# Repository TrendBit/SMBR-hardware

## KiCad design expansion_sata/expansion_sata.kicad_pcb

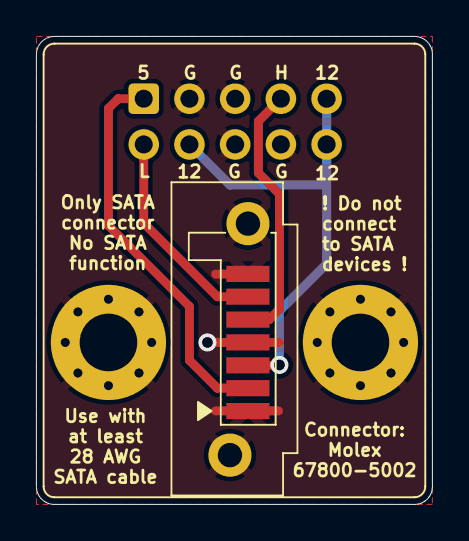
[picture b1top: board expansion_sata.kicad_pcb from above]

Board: 2 copper layers, 22.0 x 26.0 mm, 4 parts (1 on the bottom side), 5 nets.

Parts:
H1, H2: M3; MountingHole_3.2mm_M3_Pad_Via
J1: Conn_01x07_MountingPin; Molex_SATA_67800-5002_Vertical_SMD
J2: 2.54-2*5P; IDC-Header_2x05_P2.54mm_Vertical

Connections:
+5V: J1.2, J2.1
+12V: J1.3, J2.4, J2.9, J2.10
/CAN_H: J1.5, J2.7
/CAN_L: J1.6, J2.2
GND: H1.1, H2.1, J1.1, J1.4, J1.7, J1.MP (MountPin), J2.3, J2.5, J2.6, J2.8

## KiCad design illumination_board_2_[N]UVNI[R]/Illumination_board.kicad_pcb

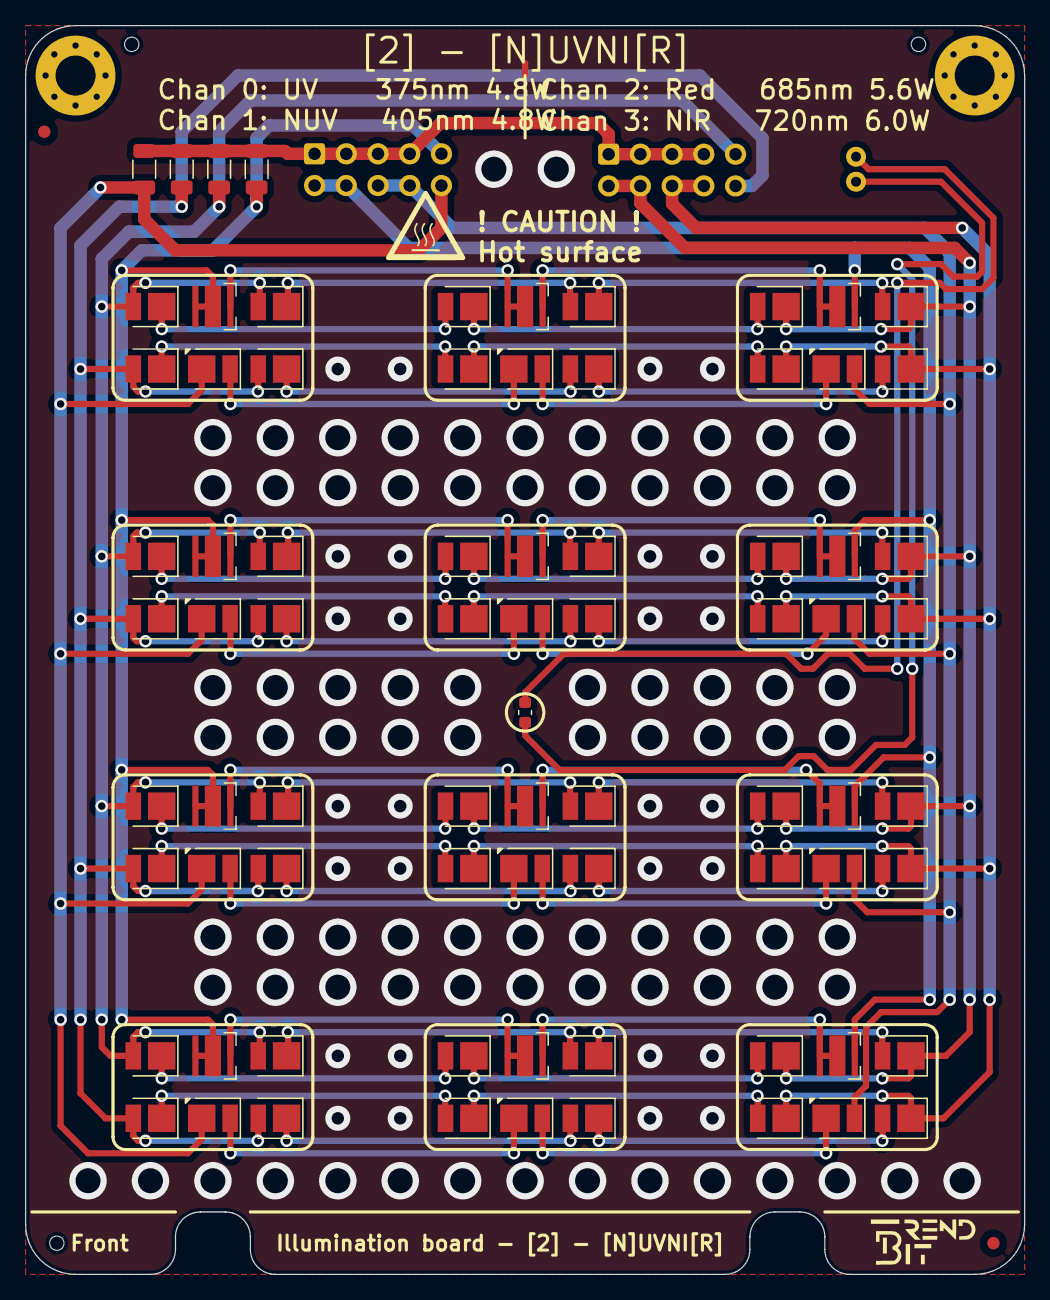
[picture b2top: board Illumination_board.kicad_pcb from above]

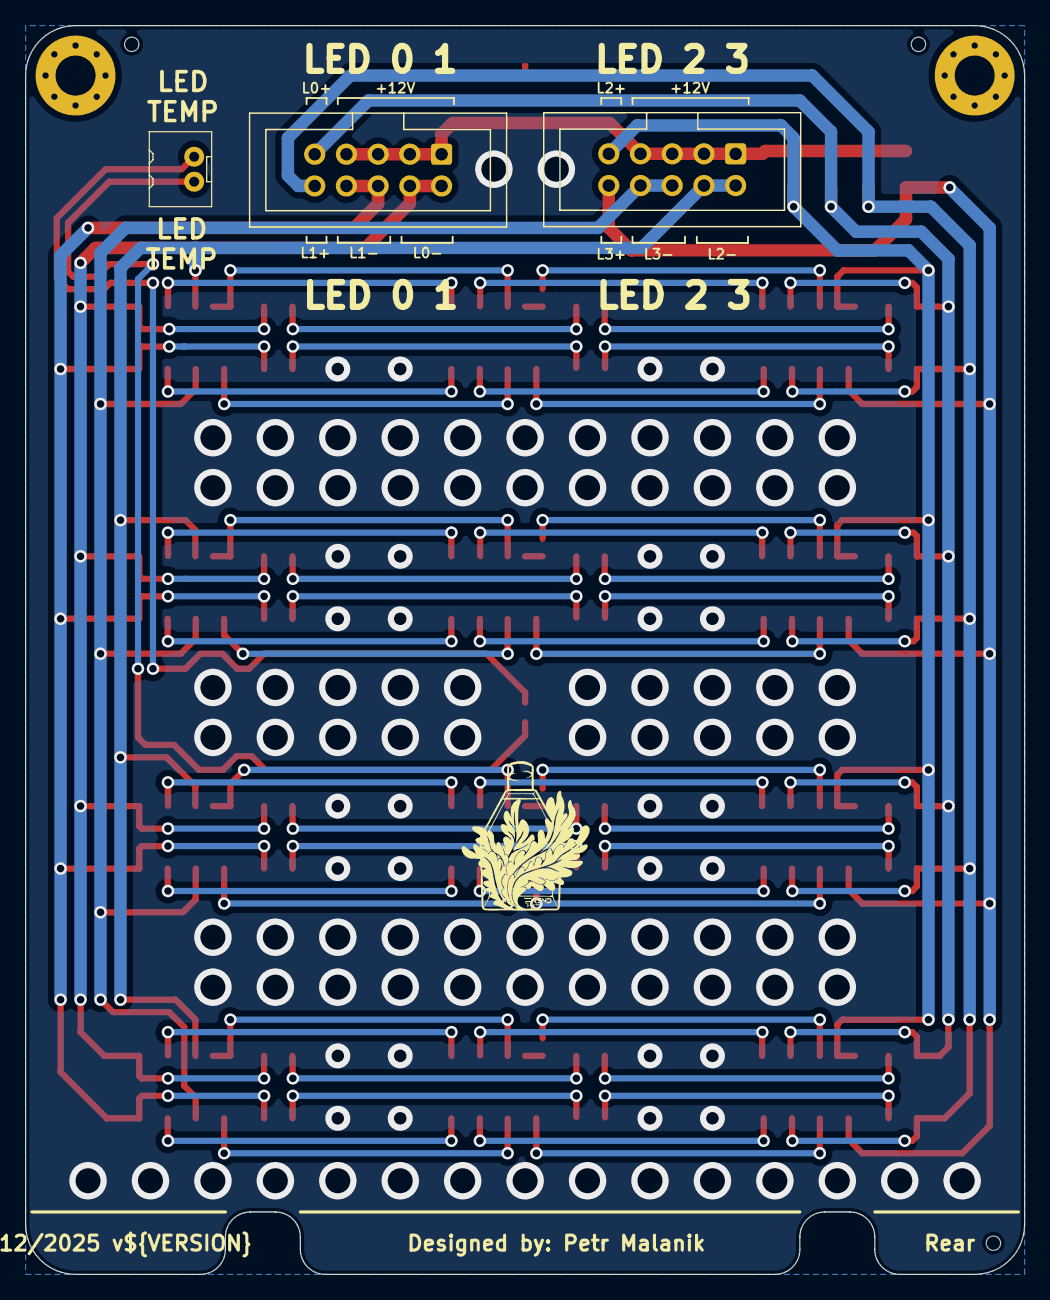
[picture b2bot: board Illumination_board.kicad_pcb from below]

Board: 2 copper layers, 80.0 x 100.0 mm, 88 parts (3 on the bottom side), 60 nets.

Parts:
D1, D2, D3, D4, D5, D6, D7, D8, D9, D10, D11, D12, D13, D14, D15, D16, D17, D18, D19, D20, D21, D22, D23, D24: XL-2835UVA-02; LED_PLCC_2835
D25, D26, D27, D28, D29, D30, D31, D32, D33, D34, D35, D36, D37, D38, D39, D40, D41, D42, D43, D44, D45, D46, D47, D48: P2835P1UVS3G12; LED_PLCC_2835
D49, D50, D51, D52, D53, D54, D55, D56, D57, D58, D59, D60: LEHR0113W120; LED_LEHR01113E-XHP35_3.5mmx3.5mm
D61, D62, D63, D64, D65, D66, D67, D68, D69, D70, D71, D72: JE2835AFR; LED_PLCC_2835_Reversed
FID1, FID2, FID3: TLH; ToolingHole_JLCPCB
FID4, FID5: 0.5/1mm; Fiducial_1mm_Mask2mm
H1, H2: M3; MountingHole_3.2mm_M3_Pad_Via
J1: DF3A-2P-2DSA; Hirose_DF3A-02P-2DSA_1x02_P2.00mm_Vertical
J2, J3: 2.54-2*5P; IDC-Header_2x05_P2.54mm_Vertical
NT1: Slug; NetTie-2_SMD_Pad0.5mm
R1, R2: 220mR; R_1206_3216Metric
R3, R4: 120mR; R_1206_3216Metric
TH1: 10k, 3950b; L_0603_1608Metric

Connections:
+12V: J2.1, J2.3, J2.5, J2.7, J3.1, J3.3, J3.5, J3.7, R1.1, R2.1, R3.1, R4.1
/LED_0+: D1.2 (A), D4.2 (A), D7.2 (A), D10.2 (A), D13.2 (A), D16.2 (A), D19.2 (A), D22.2 (A), J2.9, R1.2
/LED_0-: D3.1 (K), D6.1 (K), D9.1 (K), D12.1 (K), D15.1 (K), D18.1 (K), D21.1 (K), D24.1 (K), J2.2, J2.4
/LED_1+: D25.2 (A), D28.2 (A), D31.2 (A), D34.2 (A), D37.2 (A), D40.2 (A), D43.2 (A), D46.2 (A), J2.10, R2.2
/LED_1-: D27.1 (K), D30.1 (K), D33.1 (K), D36.1 (K), D39.1 (K), D42.1 (K), D45.1 (K), D48.1 (K), J2.6, J2.8
/LED_2+: D49.2 (A), D52.2 (A), D55.2 (A), D58.2 (A), J3.9, R3.2
/LED_2-: D51.1 (K), D54.1 (K), D57.1 (K), D60.1 (K), J3.2, J3.4
/LED_3+: D61.2 (A), D64.2 (A), D67.2 (A), D70.2 (A), J3.10, R4.2
/LED_3-: D63.1 (K), D66.1 (K), D69.1 (K), D72.1 (K), J3.6, J3.8
/SLUG: NT1.1, NT1.2
unnamed: D1.1 (K), D2.2 (A)
unnamed: D2.1 (K), D3.2 (A)
unnamed: D4.1 (K), D5.2 (A)
unnamed: D5.1 (K), D6.2 (A)
unnamed: D7.1 (K), D8.2 (A)
unnamed: D8.1 (K), D9.2 (A)
unnamed: D10.1 (K), D11.2 (A)
unnamed: D11.1 (K), D12.2 (A)
unnamed: D13.1 (K), D14.2 (A)
unnamed: D14.1 (K), D15.2 (A)
unnamed: D16.1 (K), D17.2 (A)
unnamed: D17.1 (K), D18.2 (A)
unnamed: D19.1 (K), D20.2 (A)
unnamed: D20.1 (K), D21.2 (A)
unnamed: D22.1 (K), D23.2 (A)
unnamed: D23.1 (K), D24.2 (A)
unnamed: D25.1 (K), D26.2 (A)
unnamed: D26.1 (K), D27.2 (A)
unnamed: D28.1 (K), D29.2 (A)
unnamed: D29.1 (K), D30.2 (A)
unnamed: D31.1 (K), D32.2 (A)
unnamed: D32.1 (K), D33.2 (A)
unnamed: D34.1 (K), D35.2 (A)
unnamed: D35.1 (K), D36.2 (A)
unnamed: D37.1 (K), D38.2 (A)
unnamed: D38.1 (K), D39.2 (A)
unnamed: D40.1 (K), D41.2 (A)
unnamed: D41.1 (K), D42.2 (A)
unnamed: D43.1 (K), D44.2 (A)
unnamed: D44.1 (K), D45.2 (A)
unnamed: D46.1 (K), D47.2 (A)
unnamed: D47.1 (K), D48.2 (A)
unnamed: D49.1 (K), D50.2 (A)
unnamed: D50.1 (K), D51.2 (A)
unnamed: D52.1 (K), D53.2 (A)
unnamed: D53.1 (K), D54.2 (A)
unnamed: D55.1 (K), D56.2 (A)
unnamed: D56.1 (K), D57.2 (A)
unnamed: D58.1 (K), D59.2 (A)
unnamed: D59.1 (K), D60.2 (A)
unnamed: D61.1 (K), D62.2 (A)
unnamed: D62.1 (K), D63.2 (A)
unnamed: D64.1 (K), D65.2 (A)
unnamed: D65.1 (K), D66.2 (A)
unnamed: D67.1 (K), D68.2 (A)
unnamed: D68.1 (K), D69.2 (A)
unnamed: D70.1 (K), D71.2 (A)
unnamed: D71.1 (K), D72.2 (A)
unnamed: J1.1, TH1.1
unnamed: J1.2, TH1.2
